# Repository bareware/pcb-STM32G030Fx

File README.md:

# pcb-STM32G030Fx
STM32G030Fx Development Board

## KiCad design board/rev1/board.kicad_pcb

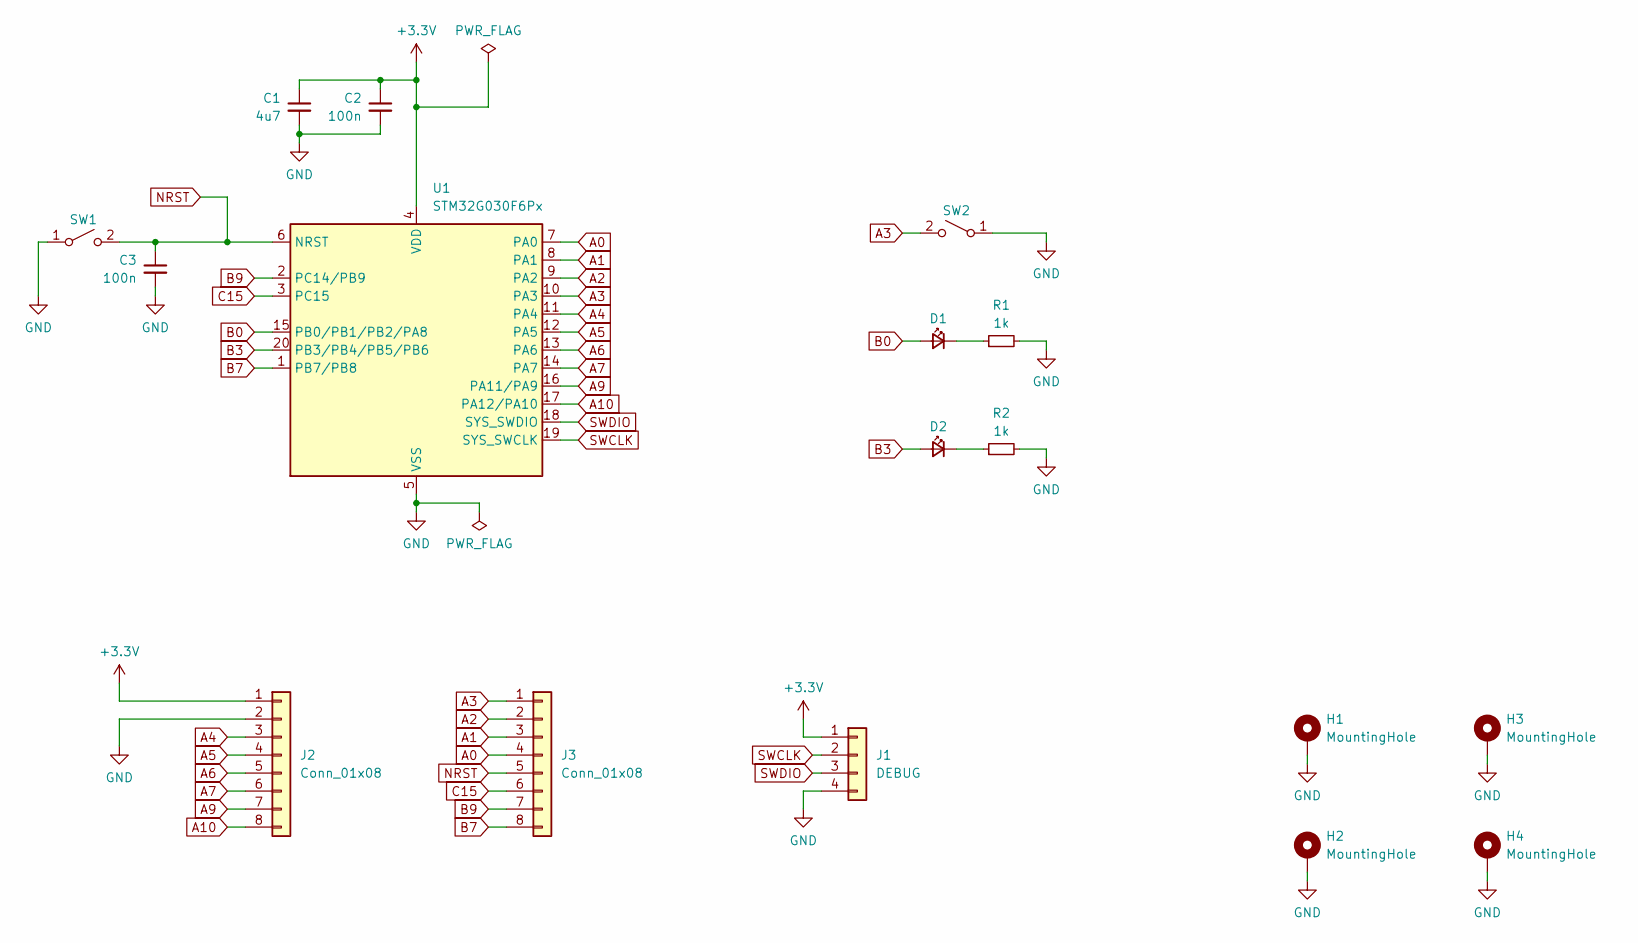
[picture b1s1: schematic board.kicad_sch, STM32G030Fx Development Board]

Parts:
C1: 4u7; C_0402_1005Metric; LCSC Part# C23733
C2, C3: 100n; C_0402_1005Metric; LCSC Part# C1525
D1, D2: LED_0603_1608Metric; LCSC Part# C2286
H1, H2, H3, H4: MountingHole; MountingHole_2.2mm_M2_Pad_Via
J1: DEBUG; PinHeader_1x04_P2.54mm_Vertical
J2, J3: Conn_01x08; PinHeader_1x08_P2.54mm_Vertical
R1, R2: 1k; R_0402_1005Metric; LCSC Part# C11702
SW1, SW2: SW_SPST_TS-1088-xR020; LCSC Part# C720477
U1: STM32G030F6Px; TSSOP-20_4.4x6.5mm_P0.65mm; LCSC Part# C529330

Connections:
+3.3V: C1.1, C2.1, J1.1, J2.1, U1.4 (VDD)
A0: J3.4, U1.7 (PA0)
A1: J3.3, U1.8 (PA1)
A2: J3.2, U1.9 (PA2)
A3: J3.1, SW2.2 (B), U1.10 (PA3)
A4: J2.3, U1.11 (PA4)
A5: J2.4, U1.12 (PA5)
A6: J2.5, U1.13 (PA6)
A7: J2.6, U1.14 (PA7)
A9: J2.7, U1.16 (PA11/PA9)
A10: J2.8, U1.17 (PA12/PA10)
B0: D1.2 (A), U1.15 (PB0/PB1/PB2/PA8)
B3: D2.2 (A), U1.20 (PB3/PB4/PB5/PB6)
B7: J3.8, U1.1 (PB7/PB8)
B9: J3.7, U1.2 (PC14/PB9)
C15: J3.6, U1.3 (PC15)
GND: C1.2, C2.2, C3.2, H1.1, H2.1, H3.1, H4.1, J1.4, J2.2, R1.2, R2.2, SW1.1 (A), SW2.1 (A), U1.5 (VSS)
NRST: C3.1, J3.5, SW1.2 (B), U1.6 (NRST)
unnamed: D1.1 (K), R1.1
unnamed: D2.1 (K), R2.1
SWCLK: J1.2, U1.19 (SYS_SWCLK)
SWDIO: J1.3, U1.18 (SYS_SWDIO)

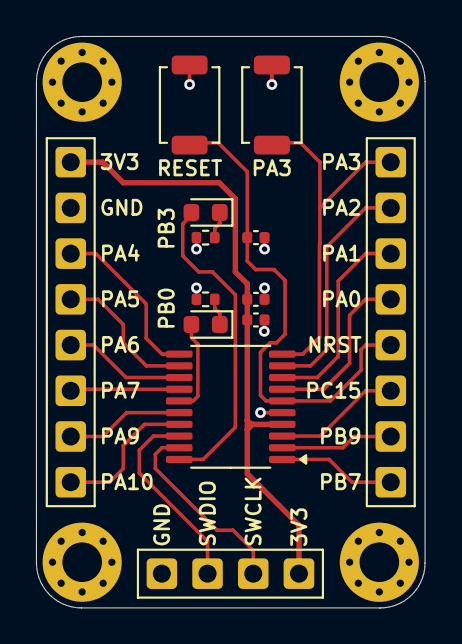
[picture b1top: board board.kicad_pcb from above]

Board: 2 copper layers, 21.6 x 31.8 mm, 17 parts (0 on the bottom side), 22 nets.

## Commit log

2026-03-10 Revision 1
2026-03-10 Adding rendering of the final board
2026-03-11 Small improvements
2026-03-11 Panelization script
2026-03-11 Image path changed
2026-03-11 Upgrading to KiCad 9
2026-03-11 Generated panel
2026-03-11 Gerbers + bom and placement for jlcpcb
